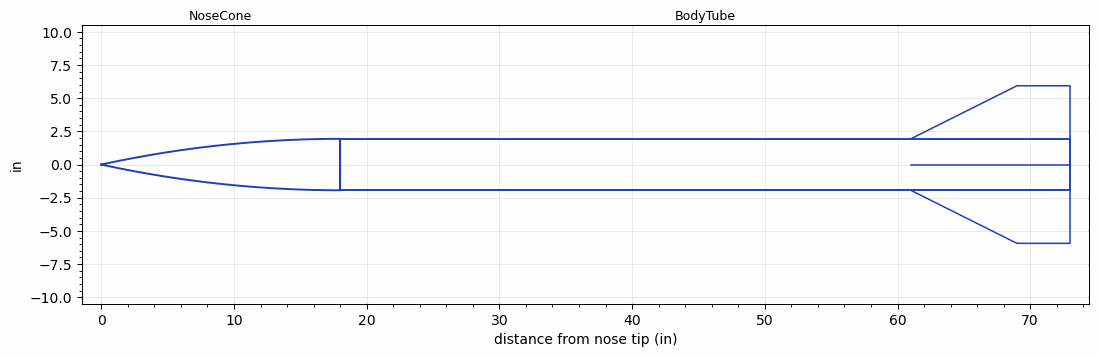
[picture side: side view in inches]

<RASAeroDocument>
 <FileVersion>2</FileVersion>
 <RocketDesign>
  <NoseCone>
   <Length>18</Length>
   <Diameter>3.875</Diameter>
   <Shape>Tangent Ogive</Shape>
   <Location>0</Location>
  </NoseCone>
  <BodyTube>
   <Length>55</Length>
   <Diameter>3.875</Diameter>
   <Location>18</Location>
   <Fin>
    <Count>4</Count>
    <Chord>12</Chord>
    <Span>4</Span>
    <SweepDistance>8</SweepDistance>
    <TipChord>4</TipChord>
    <Thickness>0.4</Thickness>
    <Location>12</Location>
    <AirfoilSection>Double Wedge</AirfoilSection>
    <FX1>4</FX1>
    <FX3>4</FX3>
   </Fin>
  </BodyTube>
  <Surface>Smooth (Zero Roughness)</Surface>
  <ModifiedBarrowman>False</ModifiedBarrowman>
  <Turbulence>False</Turbulence>
  <UseBooster1>False</UseBooster1>
  <UseBooster2>False</UseBooster2>
 </RocketDesign>
 <LaunchSite>
  <Altitude>1214</Altitude>
  <Pressure>30.18</Pressure>
  <RodAngle>6</RodAngle>
  <RodLength>15</RodLength>
  <Temperature>59</Temperature>
  <WindSpeed>9.32</WindSpeed>
 </LaunchSite>
 <Recovery>
  <Altitude1>1000</Altitude1>
  <Altitude2>1000</Altitude2>
  <DeviceType1>None</DeviceType1>
  <DeviceType2>None</DeviceType2>
  <Event1>False</Event1>
  <Event2>False</Event2>
  <Size1>1</Size1>
  <Size2>1</Size2>
  <EventType1>None</EventType1>
  <EventType2>None</EventType2>
  <CD1>1.33</CD1>
  <CD2>1.33</CD2>
 </Recovery>
 <SimulationList>
  <Simulation>
   <SustainerEngine>O3400-IM-P  (CTI)</SustainerEngine>
   <SustainerLaunchWt>50</SustainerLaunchWt>
   <SustainerCG>40</SustainerCG>
   <SustainerIgnitionDelay>0</SustainerIgnitionDelay>
   <Booster1SeparationDelay>0</Booster1SeparationDelay>
   <Booster1IgnitionDelay>0</Booster1IgnitionDelay>
   <IncludeBooster1>False</IncludeBooster1>
   <Booster2Delay>0</Booster2Delay>
   <IncludeBooster2>False</IncludeBooster2>
   <TimetoApogee>53.0971</TimetoApogee>
   <MaxAltitude>56500.02</MaxAltitude>
   <MaxVelocity>3138.147</MaxVelocity>
  </Simulation>
 </SimulationList>
</RASAeroDocument>
